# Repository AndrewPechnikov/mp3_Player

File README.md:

Апаратний MP3-плеєр на базі мікроконтролера STM32F401 з виводом високоякісного звуку через інтерфейс I2S та програмним декодуванням.

Про проєкт
Проєкт розроблено з метою адаптації класичних аудіосистем до сучасних цифрових форматів. Пристрій зчитує аудіофайли з SD-карти, програмно декодує MP3-потік за допомогою бібліотеки Helix та відправляє його на ЦАП PCM5102. Для забезпечення безперервного потокового відтворення без "заїкань" реалізовано Ping-Pong буферизацію через DMA у зв'язці з операційною системою реального часу FreeRTOS.

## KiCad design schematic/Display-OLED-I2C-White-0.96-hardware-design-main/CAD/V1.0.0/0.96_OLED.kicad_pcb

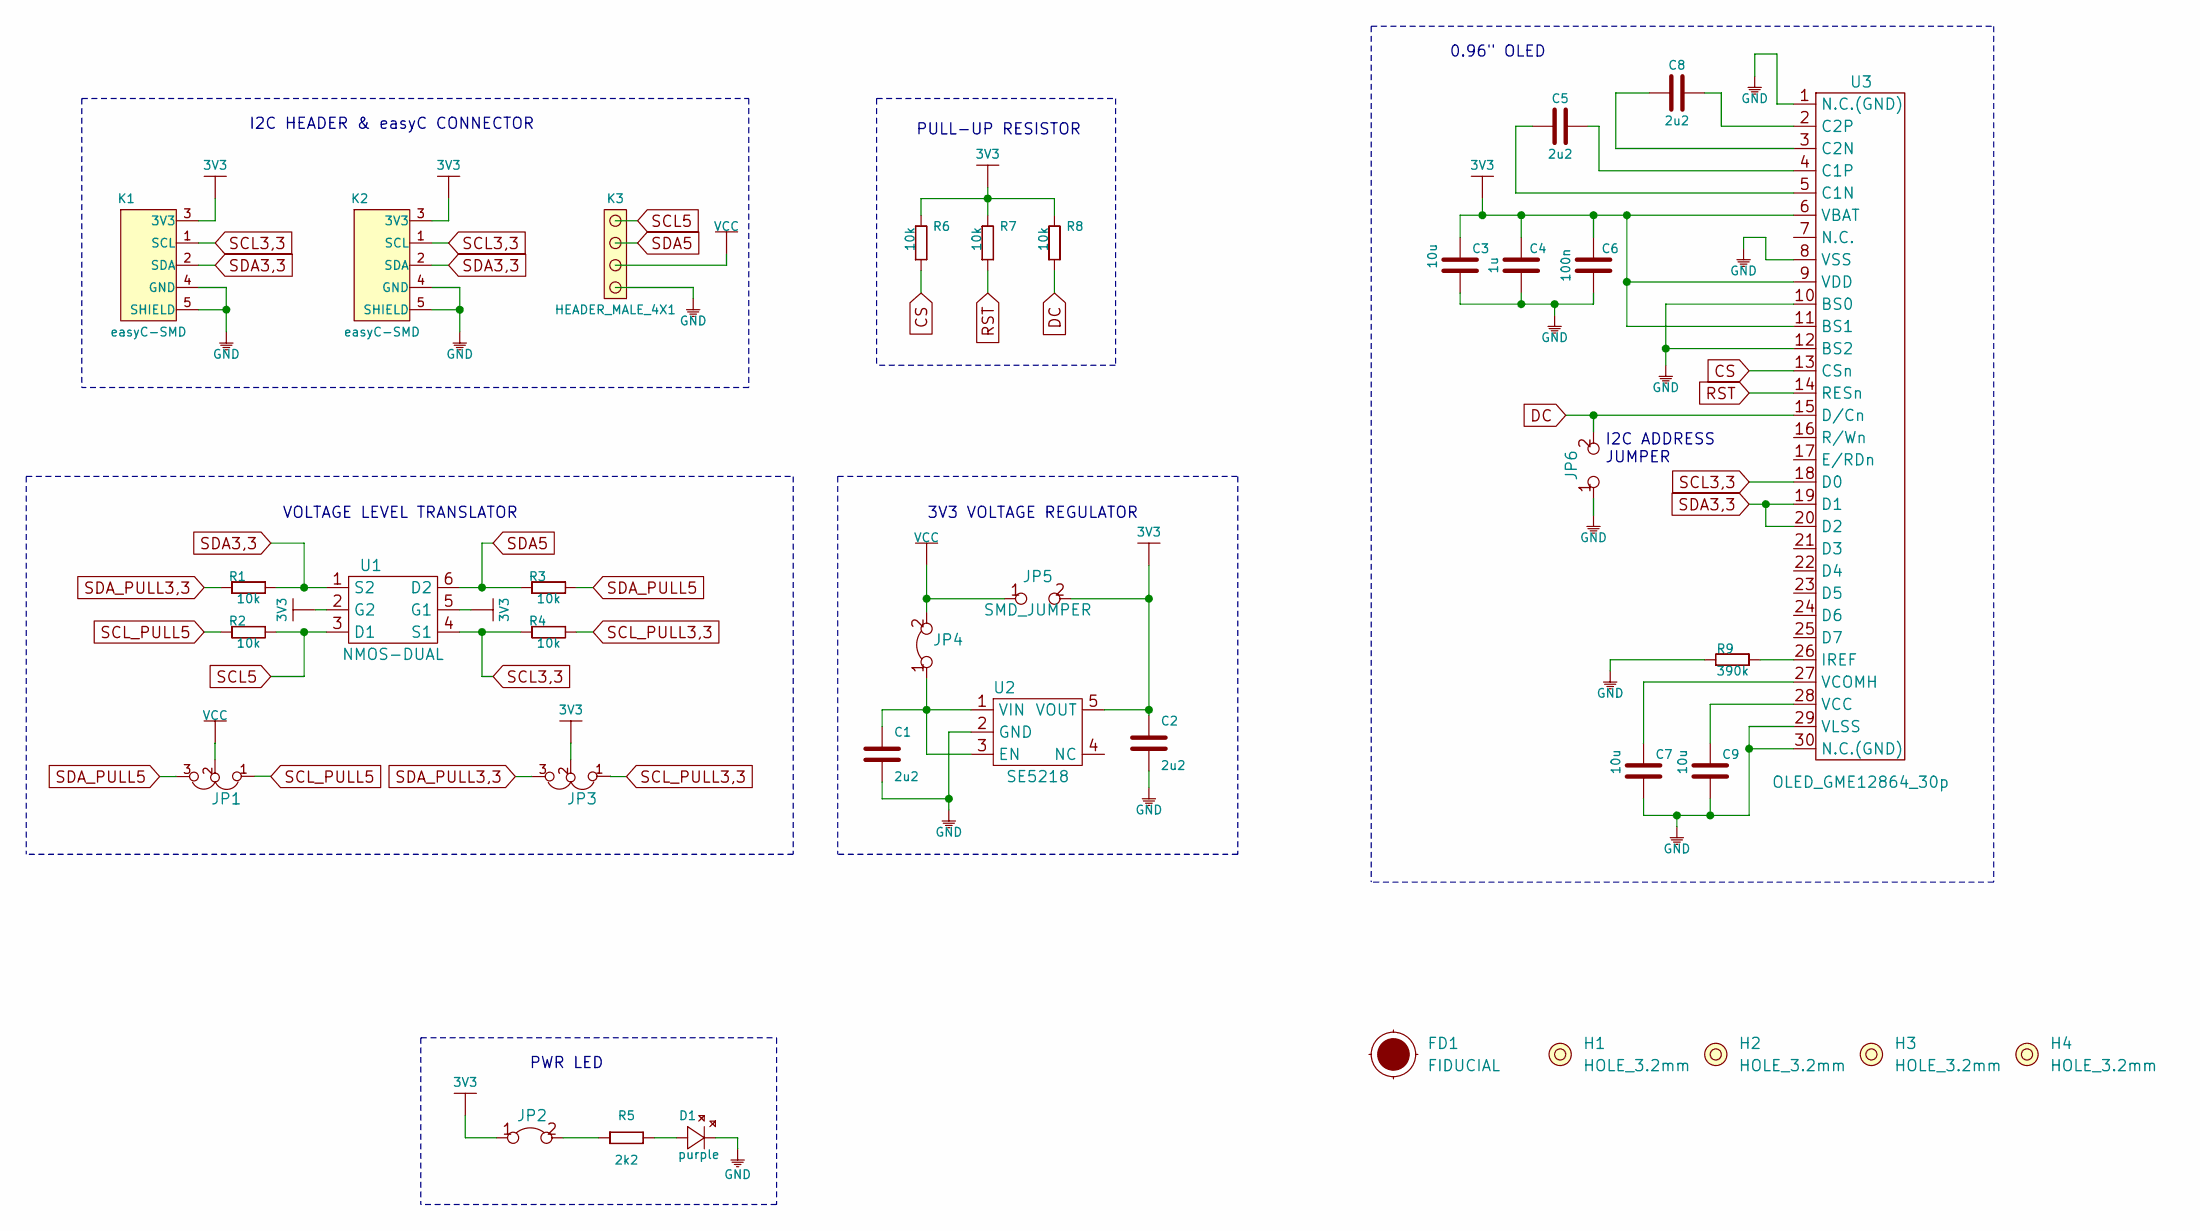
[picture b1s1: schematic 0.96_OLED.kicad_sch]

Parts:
C1, C2, C5, C8: 2u2; 0603C
C3, C7, C9: 10u; 1206C
C4: 1u; 0603C
C6: 100n; 0603C
D1: purple; 0402LED
FD1: FIDUCIAL; FIDUCIAL_23
H1, H2, H3, H4: HOLE_3.2mm
JP1, JP3: SMD_JUMPER_3_PAD_TRACE
JP2, JP4: SMD-JUMPER-CONNECTED_TRACE_SLODERMASK
JP5, JP6: SMD_JUMPER
K1, K2: easyC-SMD; easyC-connector
K3: HEADER_MALE_4X1
R1, R2, R3, R4, R6, R7, R8: 10k; 0603R
R5: 2k2; 0402R
R9: 390k; 0603R
U1: NMOS-DUAL; SOT-363
U2: SE5218; SOT-23-5
U3: OLED_GME12864_30p; OLED_GME128x64_30p

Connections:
3V3: C2.2, C3.1, C4.1, C6.1, JP2.1, JP3.2, JP5.2, K1.3 (3V3), K2.3 (3V3), R6.2, R7.2, R8.2, U1.2 (G2), U1.5 (G1), U2.5 (VOUT), U3.6 (VBAT), U3.9 (VDD), U3.11 (BS1)
CS: R6.1, U3.13 (CSn)
DC: JP6.2, R8.1, U3.15 (D/Cn)
GND: C1.1, C2.1, C3.2, C4.2, C6.2, C7.2, C9.2, D1.2 (K), JP6.1, K1.4 (GND), K1.5 (SHIELD), K2.4 (GND), K2.5 (SHIELD), K3.1, R9.2, U2.2 (GND), U3.1 (N.C.(GND)), U3.8 (VSS), U3.10 (BS0), U3.12 (BS2), U3.29 (VLSS), U3.30 (N.C.(GND))
unnamed: C1.2, JP4.1, U2.1 (VIN), U2.3 (EN)
unnamed: C5.1, U3.5 (C1N)
unnamed: C5.2, U3.4 (C1P)
unnamed: C7.1, U3.27 (VCOMH)
unnamed: C8.1, U3.3 (C2N)
unnamed: C8.2, U3.2 (C2P)
unnamed: C9.1, U3.28 (VCC)
unnamed: D1.1 (A), R5.2
unnamed: JP2.2, R5.1
unnamed: R9.1, U3.26 (IREF)
RST: R7.1, U3.14 (RESn)
SCL3,3: K1.1 (SCL), K2.1 (SCL), R4.1, U1.4 (S1), U3.18 (D0)
SCL5: K3.4, R2.2, U1.3 (D1)
SCL_PULL3,3: JP3.1, R4.2
SCL_PULL5: JP1.1, R2.1
SDA3,3: K1.2 (SDA), K2.2 (SDA), R1.2, U1.1 (S2), U3.19 (D1), U3.20 (D2)
SDA5: K3.3, R3.1, U1.6 (D2)
SDA_PULL3,3: JP3.3, R1.1
SDA_PULL5: JP1.3, R3.2
VCC: JP1.2, JP4.2, JP5.1, K3.2

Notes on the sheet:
I2C HEADER & easyC CONNECTOR
VOLTAGE LEVEL TRANSLATOR
PWR LED
PULL-UP RESISTOR
3V3 VOLTAGE REGULATOR
0.96" OLED
I2C ADDRESS JUMPER

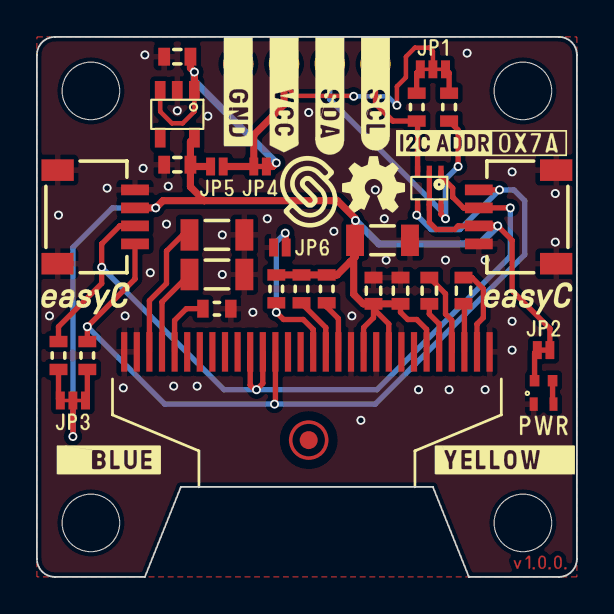
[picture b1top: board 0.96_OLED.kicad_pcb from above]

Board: 2 copper layers, 30.0 x 30.0 mm, 37 parts (0 on the bottom side), 24 nets.

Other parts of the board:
Ref**: Val**; Version1.0.0.

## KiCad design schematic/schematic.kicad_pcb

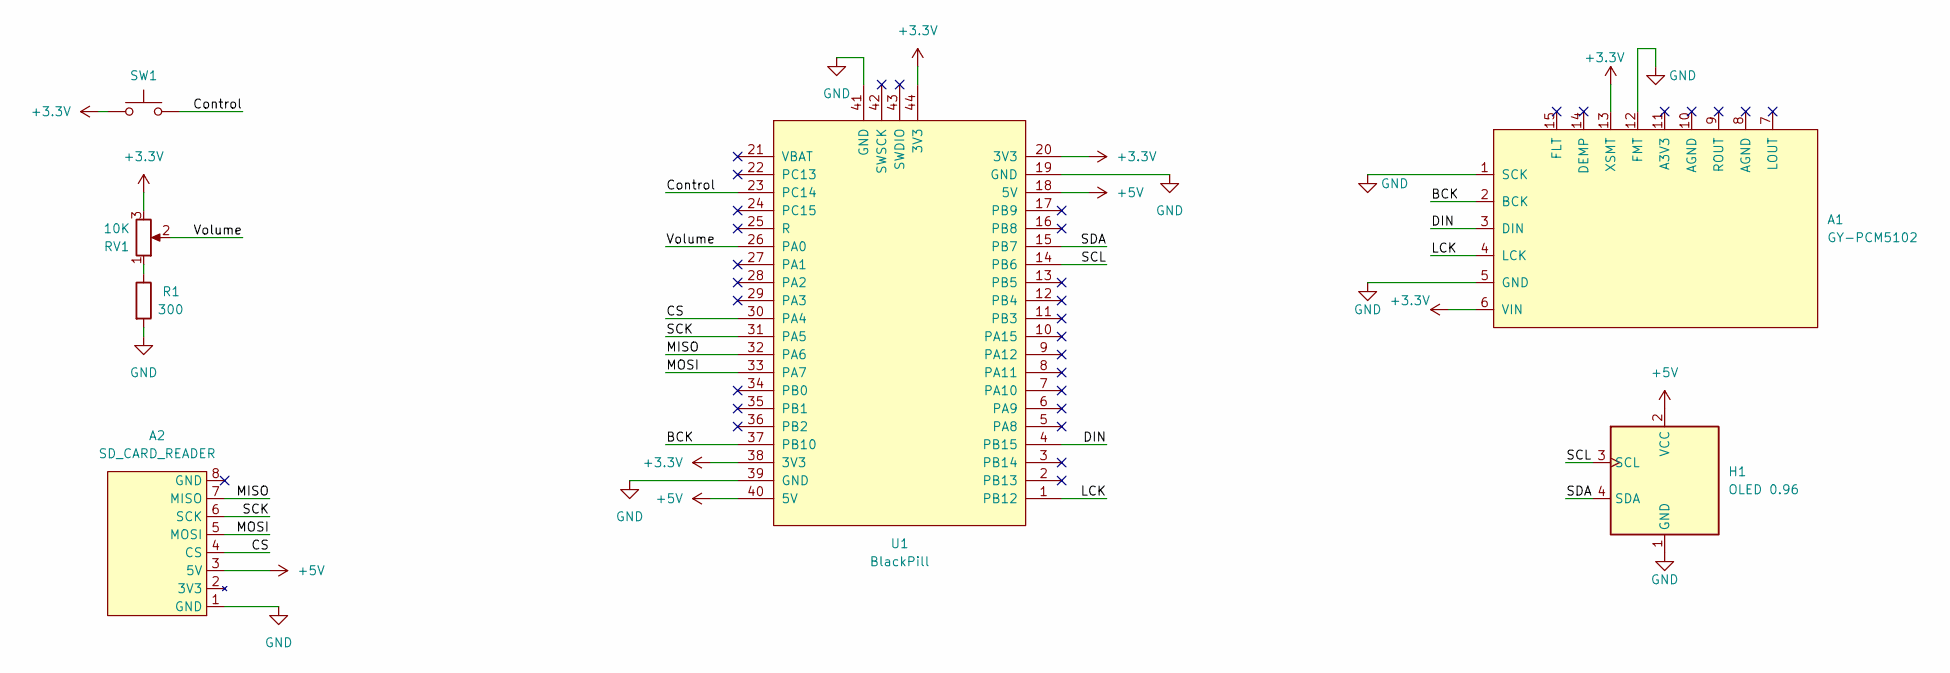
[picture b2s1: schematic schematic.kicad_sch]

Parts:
A1: GY-PCM5102
A2: SD_CARD_READER; PinHeader_1x08_P2.54mm_Vertical
H1: OLED 0.96; PinHeader_1x04_P2.54mm_Vertical
R1: R; R_Axial_DIN0204_L3.6mm_D1.6mm_P7.62mm_Horizontal
RV1: R_Potentiometer; Potentiometer_Piher_T-16H_Single_Horizontal
SW1: SW_Omron_B3FS; SW_SPST_Omron_B3FS-100xP
U1: BlackPill; YAAJ_BluePill_SWD_2

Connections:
+3.3V: A1.6 (VIN), A1.13 (XSMT), RV1.3, SW1.1, U1.20 (3V3), U1.38 (3V3), U1.44 (3V3)
+5V: A2.3 (5V), H1.2 (VCC), U1.18 (5V), U1.40 (5V)
/BCK: A1.2 (BCK), U1.37 (PB10)
/CS: A2.4 (CS), U1.30 (PA4)
/Control: SW1.2, U1.23 (PC14)
/DIN: A1.3 (DIN), U1.4 (PB15)
/LCK: A1.4 (LCK), U1.1 (PB12)
/MISO: A2.7 (MISO), U1.32 (PA6)
/MOSI: A2.5 (MOSI), U1.33 (PA7)
/SCK: A2.6 (SCK), U1.31 (PA5)
/SCL: H1.3 (SCL), U1.14 (PB6)
/SDA: H1.4 (SDA), U1.15 (PB7)
/Volume: RV1.2, U1.26 (PA0)
GND: A1.1 (SCK), A1.5 (GND), A1.12 (FMT), A2.1 (GND), H1.1 (GND), R1.2, U1.19 (GND), U1.39 (GND), U1.41 (GND)
unnamed: R1.1, RV1.1

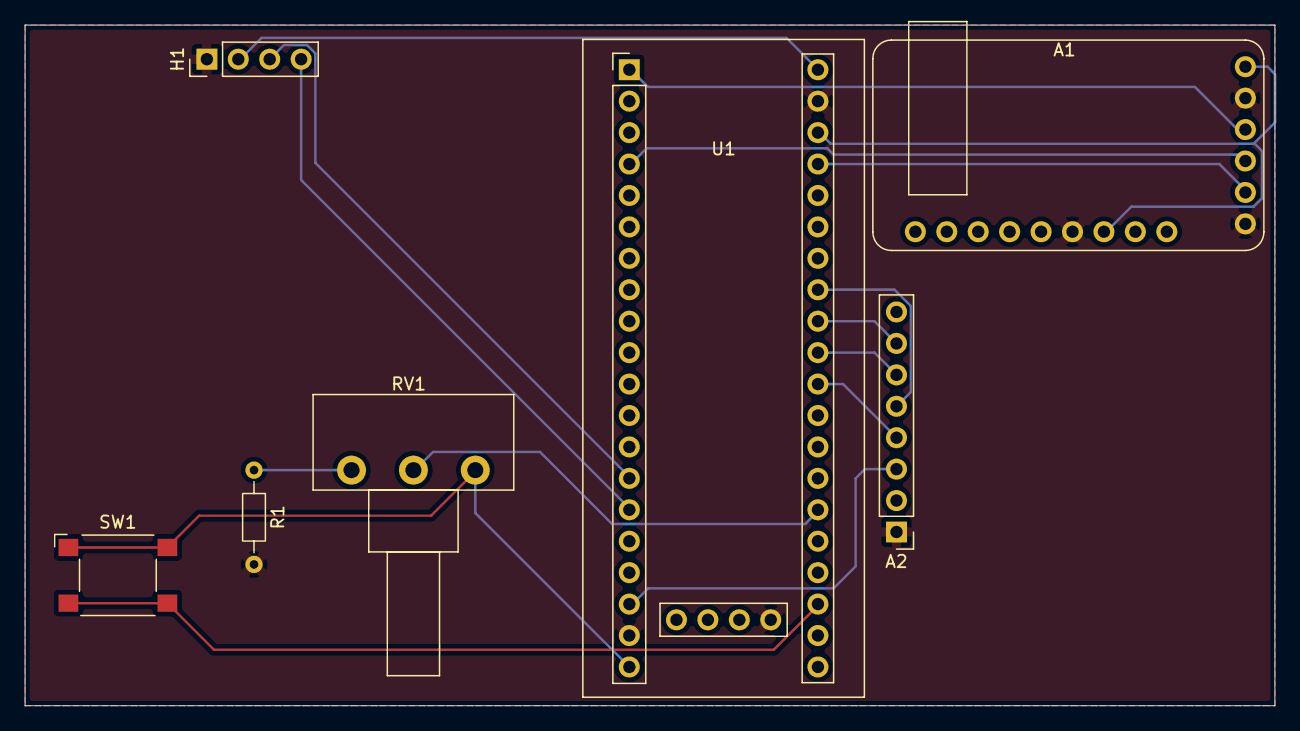
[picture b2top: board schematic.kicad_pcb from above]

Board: 2 copper layers, 101.0 x 55.0 mm, 7 parts (0 on the bottom side), 15 nets.

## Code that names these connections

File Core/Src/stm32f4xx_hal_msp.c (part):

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
    __HAL_RCC_GPIOA_CLK_ENABLE();
    /**ADC1 GPIO Configuration
    PA0-WKUP     ------> ADC1_IN0
    */
    GPIO_InitStruct.Pin = GPIO_PIN_0;
    GPIO_InitStruct.Mode = GPIO_MODE_ANALOG;
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    __HAL_RCC_ADC1_CLK_DISABLE();

    /**ADC1 GPIO Configuration
    PA0-WKUP     ------> ADC1_IN0
    */
    HAL_GPIO_DeInit(GPIOA, GPIO_PIN_0);

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
    __HAL_RCC_GPIOB_CLK_ENABLE();
    /**I2C1 GPIO Configuration
    PB6     ------> I2C1_SCL
    PB7     ------> I2C1_SDA
    */
    GPIO_InitStruct.Pin = GPIO_PIN_6|GPIO_PIN_7;
    GPIO_InitStruct.Mode = GPIO_MODE_AF_OD;
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    __HAL_RCC_I2C1_CLK_DISABLE();

    /**I2C1 GPIO Configuration
    PB6     ------> I2C1_SCL
    PB7     ------> I2C1_SDA
    */
    HAL_GPIO_DeInit(GPIOB, GPIO_PIN_6);

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
    __HAL_RCC_GPIOB_CLK_ENABLE();
    /**I2S2 GPIO Configuration
    PB10     ------> I2S2_CK
    PB12     ------> I2S2_WS
    PB15     ------> I2S2_SD
    */
    GPIO_InitStruct.Pin = GPIO_PIN_10|GPIO_PIN_12|GPIO_PIN_15;
    GPIO_InitStruct.Mode = GPIO_MODE_AF_PP;
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    __HAL_RCC_SPI2_CLK_DISABLE();

    /**I2S2 GPIO Configuration
    PB10     ------> I2S2_CK
    PB12     ------> I2S2_WS
    PB15     ------> I2S2_SD
    */
    HAL_GPIO_DeInit(GPIOB, GPIO_PIN_10|GPIO_PIN_12|GPIO_PIN_15);

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
    __HAL_RCC_GPIOA_CLK_ENABLE();
    /**SPI1 GPIO Configuration
    PA5     ------> SPI1_SCK
    PA6     ------> SPI1_MISO
    PA7     ------> SPI1_MOSI
    */
    GPIO_InitStruct.Pin = GPIO_PIN_5|GPIO_PIN_6|GPIO_PIN_7;
    GPIO_InitStruct.Mode = GPIO_MODE_AF_PP;
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    __HAL_RCC_SPI1_CLK_DISABLE();

    /**SPI1 GPIO Configuration
    PA5     ------> SPI1_SCK
    PA6     ------> SPI1_MISO
    PA7     ------> SPI1_MOSI
    */
    HAL_GPIO_DeInit(GPIOA, GPIO_PIN_5|GPIO_PIN_6|GPIO_PIN_7);

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
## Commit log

2026-05-28 firsk working prototype
2026-06-15 control by one button
2026-06-15 refactor startDefaultTask v1
2026-06-15 refactor
2026-06-15 refactor v2
2026-06-15 fix bug
2026-06-19 refactor add scheme
2026-06-19 bug fix
2026-06-23 Remove detailed sections from README.md
    Removed sections on quick start, architecture, technology stack, results, and author from the README.

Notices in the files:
Core/Src/stm32f4xx_hal_msp.c:
Copyright (c) 2026 STMicroelectronics.
All rights reserved.
This software is licensed under terms that can be found in the LICENSE file
